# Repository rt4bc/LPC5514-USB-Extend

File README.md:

# LPC5514-USB-Extend
## Function
Create a board which integrated with CMSIS DAP interface for cortex MCU debugging, and extend with common digital interface, like I2C, SPI, UART, CAN, ADC, and GPIO(Including normal input and output function, also can working at bitbang mode, like FT232H chip).

## Hardware Architecture
### USB0/1 Interface
1. USB0, Full speed interface, reserved.
2. USB1, High speed interface, Custom HID device, for CMSIS-Dap interface and other extened interfaces, SPI, UART, I2C and CAN FD.
### 3D Layout

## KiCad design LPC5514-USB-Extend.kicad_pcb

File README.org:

* LPC5514-USB-Extend
** Function
Create a board which integrated with CMSIS DAP interface for cortex MCU debugging, and extend with common digital interface, like I2C, SPI, UART, CAN, ADC, and GPIO(Including normal input and output function, also can working at bitbang mode, like FT232H chip).

** Hardware Architecture
*** USB0/1 Interface
1. USB0, Full speed interface, reserved.
2. USB1, High speed interface, Custom HID device, for CMSIS-Dap interface and other extened interfaces, SPI, UART, I2C and CAN FD.
*** 3D Layout
[[file:LPC5514-USB-Extend.png][PCB 3D Layout]]

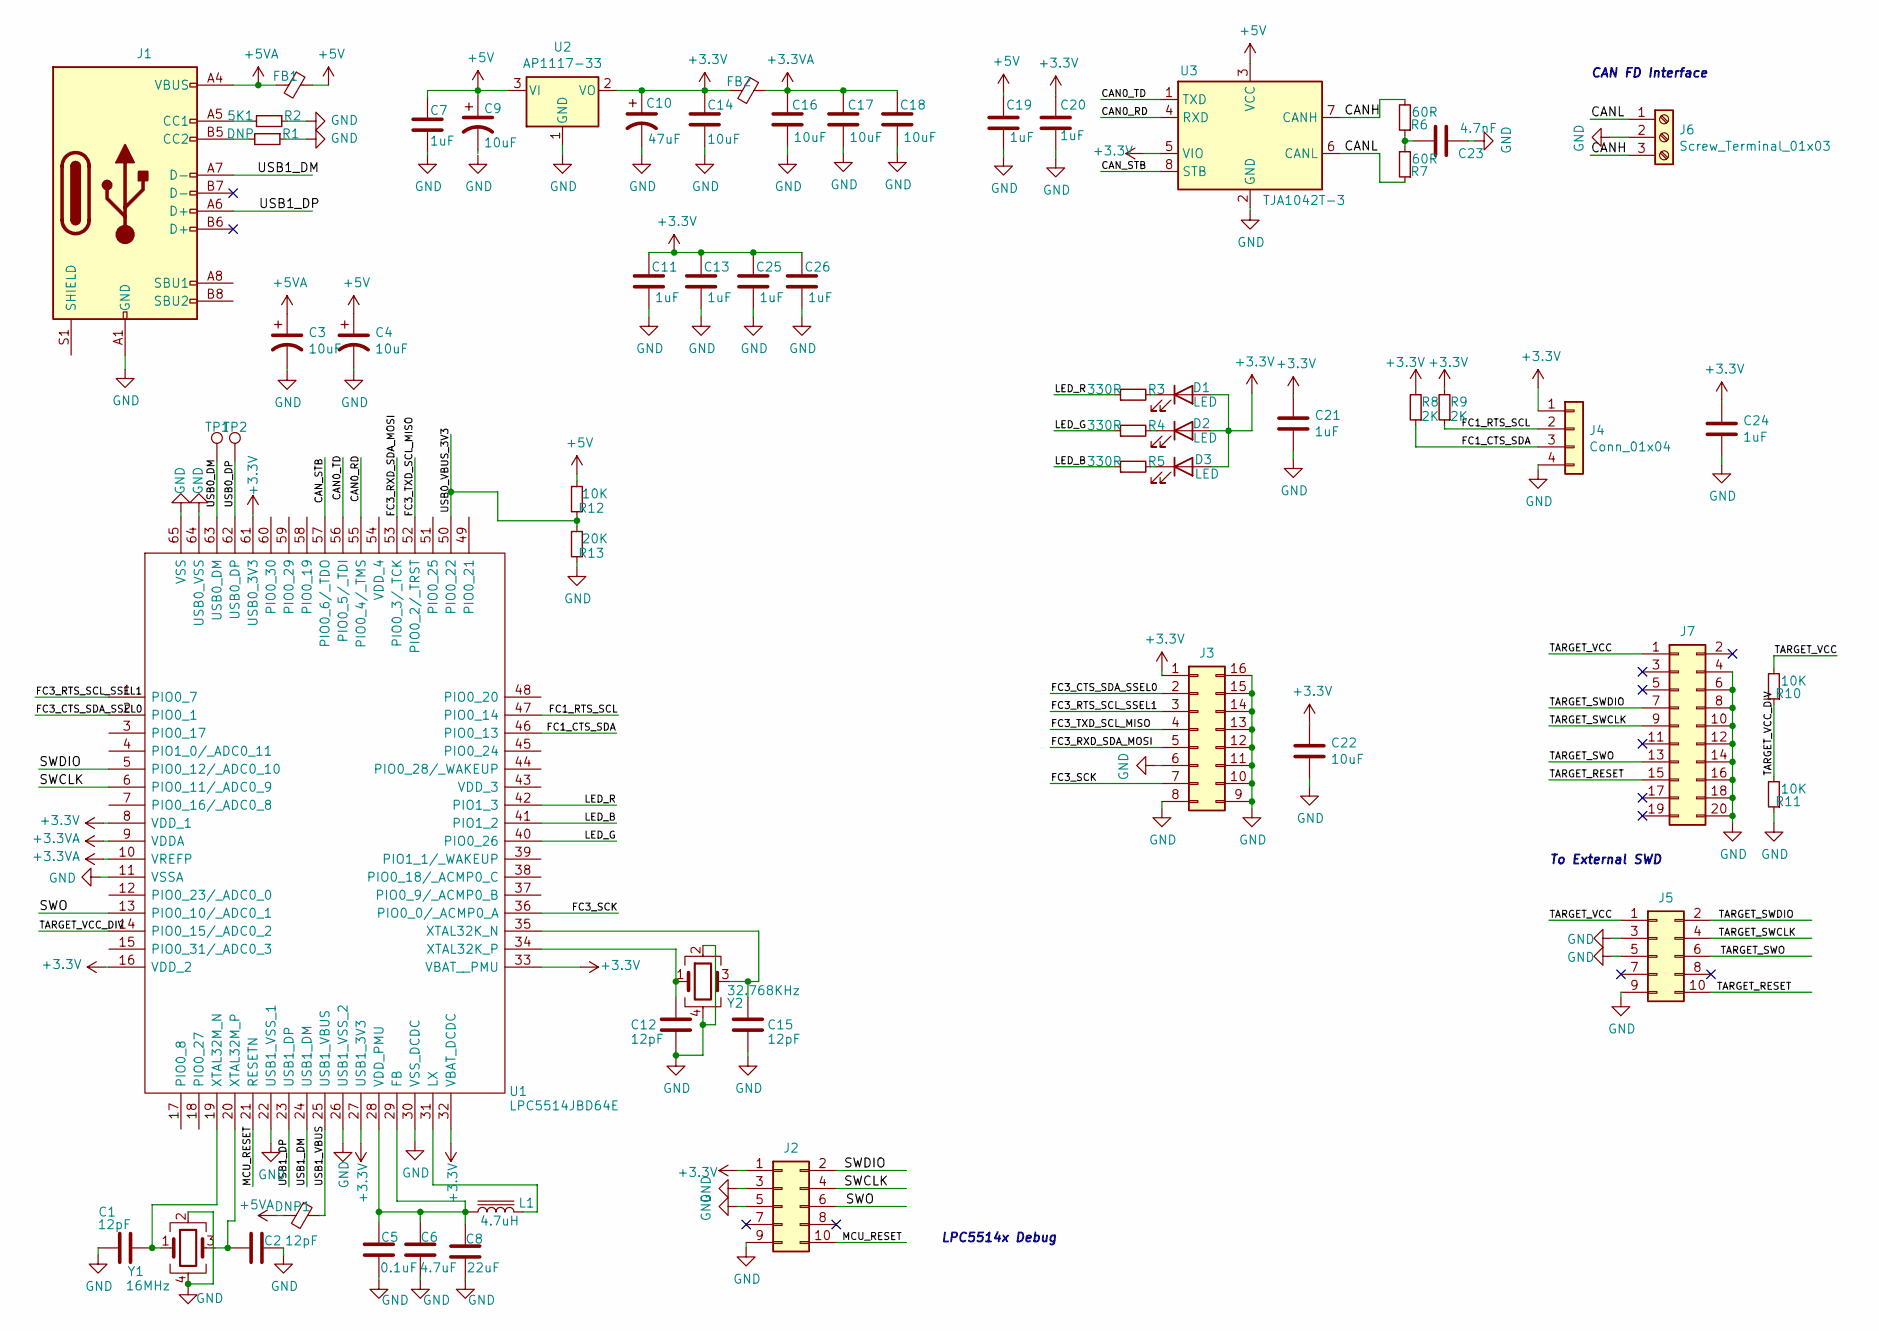
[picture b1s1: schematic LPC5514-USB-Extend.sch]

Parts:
C1, C2, C12, C15: 12pF; C_0603_1608Metric_Pad1.08x0.95mm_HandSolder
C3, C4, C9, C14, C16, C17, C18: 10uF; C_0805_2012Metric_Pad1.18x1.45mm_HandSolder
C5: 0.1uF; C_0603_1608Metric_Pad1.08x0.95mm_HandSolder
C6: 4.7uF; C_0805_2012Metric_Pad1.18x1.45mm_HandSolder
C7, C11, C13, C19, C20, C24, C25, C26: 1uF; C_0603_1608Metric_Pad1.08x0.95mm_HandSolder
C8: 22uF; C_0805_2012Metric_Pad1.18x1.45mm_HandSolder
C10: 47uF; C_0805_2012Metric_Pad1.18x1.45mm_HandSolder
C21: 1uF; C_0805_2012Metric_Pad1.18x1.45mm_HandSolder
C22: 10uF; C_0603_1608Metric_Pad1.08x0.95mm_HandSolder
C23: 4.7nF; C_0603_1608Metric_Pad1.08x0.95mm_HandSolder
D1, D2, D3: LED; LED_0603_1608Metric
DNP1: Ferrite_Bead_Small; L_0603_1608Metric
FB1, FB2: Ferrite_Bead_Small; L_0603_1608Metric
J1: USB_C_Receptacle_USB2.0; USB_C_Receptacle_HRO_TYPE-C-31-M-12
J2, J5: Conn_02x05_Odd_Even; PinHeader_2x05_P1.27mm_Vertical
J3: Conn_02x08_Counter_Clockwise; PinHeader_2x08_P2.54mm_Vertical
J4: Conn_01x04; PinHeader_1x04_P2.54mm_Vertical
J6: Screw_Terminal_01x03; PhoenixContact_MSTBA_2,5_3-G-5,08_1x03_P5.08mm_Horizontal
J7: Conn_02x10_Odd_Even; PinHeader_2x10_P2.54mm_Vertical
L1: 4.7uH; L_Wuerth_MAPI-2512
R1: DNP; R_0603_1608Metric
R2: 5K1; R_0603_1608Metric
R3, R4, R5: 330R; R_0603_1608Metric
R6, R7: 60R; R_0603_1608Metric
R8, R9: 2K; R_0603_1608Metric
R10, R11, R12: 10K; R_0603_1608Metric
R13: 20K; R_0603_1608Metric
TP1, TP2: TestPoint; TestPoint_Pad_1.0x1.0mm
U1: LPC5514JBD64E; QFP50P1200X1200X120-65N; Manufacturer_Part_Number LPC5514JBD64E; Mouser Part Number 771-LPC5514JBD64E
U2: AP1117-33; SOT-223-3_TabPin2
U3: TJA1042T-3; SOIC-8_3.9x4.9mm_P1.27mm
Y1: 16MHz; Oscillator_SMD_Abracon_ASE-4Pin_3.2x2.5mm
Y2: 32.768KHz; Oscillator_SMD_Abracon_ASE-4Pin_3.2x2.5mm

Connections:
+3.3VA: C16.1, C17.1, C18.1, FB2.1, U1.9 (VDDA), U1.10 (VREFP)
+3V3: C10.1, C11.1, C13.1, C14.1, C20.1, C21.1, C22.1, C24.1, C25.1, C26.1, D1.2 (A), D2.2 (A), D3.2 (A), FB2.2, J2.1, J3.1, J4.1, R8.2, R9.2, U1.8 (VDD_1), U1.16 (VDD_2), U1.27 (USB1_3V3), U1.32 (VBAT_DCDC), U1.33 (VBAT__PMU), U1.61 (USB0_3V3), U2.2 (VO), U3.5 (VIO)
+5V: C4.1, C7.1, C9.1, C19.1, FB1.1, R12.1, U2.3 (VI), U3.3 (VCC)
+5VA: C3.1, DNP1.2, FB1.2, J1.A4 (VBUS), J1.A9 (VBUS), J1.B4 (VBUS), J1.B9 (VBUS)
/CAN0_RD: U1.55 (PIO0_4/_TMS), U3.4 (RXD)
/CAN0_TD: U1.56 (PIO0_5/_TDI), U3.1 (TXD)
/CANH: J6.3, R6.2, U3.7 (CANH)
/CANL: J6.1, R7.1, U3.6 (CANL)
/CAN_STB: U1.57 (PIO0_6/_TDO), U3.8 (STB)
/FC1_CTS_SDA: J4.3, R8.1, U1.46 (PIO0_13)
/FC1_RTS_SCL: J4.2, R9.1, U1.47 (PIO0_14)
/FC3_CTS_SDA_SSEL0: J3.2, U1.2 (PIO0_1)
/FC3_RTS_SCL_SSEL1: J3.3, U1.1 (PIO0_7)
/FC3_RXD_SDA_MOSI: J3.5, U1.53 (PIO0_3/_TCK)
/FC3_SCK: J3.7, U1.36 (PIO0_0/_ACMP0_A)
/FC3_TXD_SCL_MISO: J3.4, U1.52 (PIO0_2/_TRST)
/LED_B: R5.1, U1.41 (PIO1_2)
/LED_G: R4.1, U1.40 (PIO0_26)
/LED_R: R3.1, U1.42 (PIO1_3)
/MCU_RESET: J2.10, U1.21 (RESETN)
/SWCLK: J2.4, U1.6 (PIO0_11/_ADC0_9)
/SWDIO: J2.2, U1.5 (PIO0_12/_ADC0_10)
/SWO: J2.6, U1.13 (PIO0_10/_ADC0_1)
/TARGET_RESET: J5.10, J7.15
/TARGET_SWCLK: J5.4, J7.9
/TARGET_SWDIO: J5.2, J7.7
/TARGET_SWO: J5.6, J7.13
/TARGET_VCC: J5.1, J7.1, R10.2
/TARGET_VCC_DIV: R10.1, R11.2, U1.14 (PIO0_15/_ADC0_2)
/USB0_DM: TP1.1, U1.63 (USB0_DM)
/USB0_DP: TP2.1, U1.62 (USB0_DP)
/USB0_VBUS_3V3: R12.2, R13.1, U1.50 (PIO0_22)
/USB1_DM: J1.A7 (D-), U1.24 (USB1_DM)
/USB1_DP: J1.A6 (D+), U1.23 (USB1_DP)
/USB1_VBUS: DNP1.1, U1.25 (USB1_VBUS)
GND: C1.2, C2.1, C3.2, C4.2, C5.1, C6.1, C7.2, C8.1, C10.2, C11.2, C12.1, C13.2, C14.2, C15.1, C16.2, C17.2, C18.2, C19.2, C20.2, C21.2, C22.2, C23.1, C24.2, C25.2, C26.2, J1.A1 (GND), J1.A12 (GND), J1.B1 (GND), J1.B12 (GND), J2.3, J2.5, J2.9, J3.6, J3.8, J3.9, J3.10, J3.11, J3.12, J3.13, J3.14, J3.15, J3.16, J4.4, J5.3, J5.5, J5.9, J6.2, J7.4, J7.6, J7.8, J7.10, J7.12, J7.14, J7.16, J7.18, J7.20, R1.1, R2.1, R11.1, R13.2, U1.11 (VSSA), U1.22 (USB1_VSS_1), U1.26 (USB1_VSS_2), U1.30 (VSS_DCDC), U1.64 (USB0_VSS), U1.65 (VSS), U2.1 (GND), U3.2 (GND), Y1.2, Y1.4, Y2.2, Y2.4
unnamed: C1.1, U1.19 (XTAL32M_N), Y1.1
unnamed: C2.2, U1.20 (XTAL32M_P), Y1.3
unnamed: C5.2, C6.2, C8.2, L1.1, U1.28 (VDD_PMU), U1.29 (FB)
unnamed: C12.2, U1.34 (XTAL32K_P), Y2.1
unnamed: C15.2, U1.35 (XTAL32K_N), Y2.3
unnamed: C23.2, R6.1, R7.2
unnamed: D1.1 (K), R3.2
unnamed: D2.1 (K), R4.2
unnamed: D3.1 (K), R5.2
unnamed: J1.A5 (CC1), R2.2
unnamed: J1.B5 (CC2), R1.2
unnamed: L1.2, U1.31 (LX)

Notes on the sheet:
To External SWD
LPC5514x Debug
CAN FD Interface

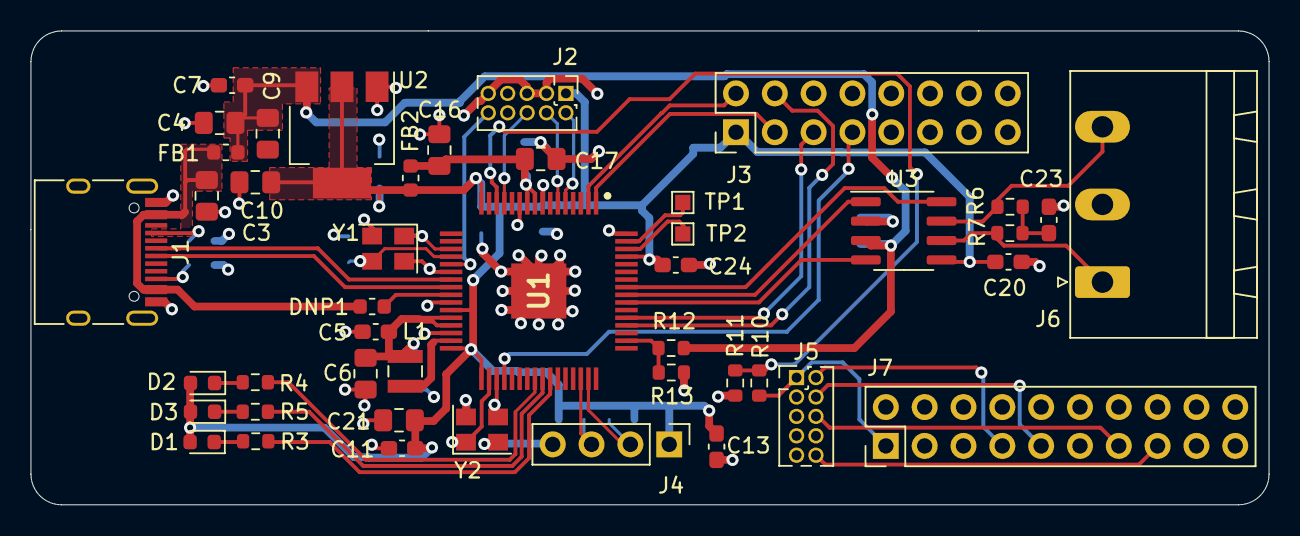
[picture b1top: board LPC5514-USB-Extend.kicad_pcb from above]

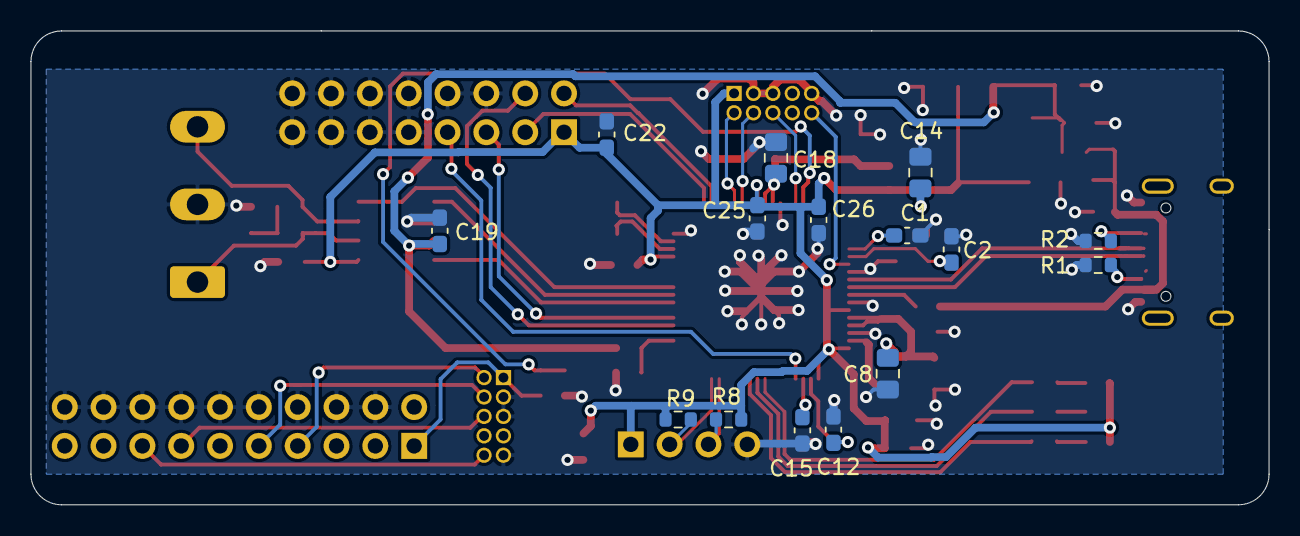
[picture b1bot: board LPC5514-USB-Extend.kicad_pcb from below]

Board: 2 copper layers, 81.0 x 31.0 mm, 60 parts (15 on the bottom side), 48 nets.

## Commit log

2021-05-27 remove unused fiels
2021-05-27 rm files
2021-05-27 rename README
2021-05-27 README.org
2021-05-28 create system document.
2021-06-06 update design, usb0/1 connection & power
2021-06-06 update description.
2021-06-15 update sch and add footprint
2021-06-16 update pcb
2021-06-20 update design
2021-06-20 Add PCB 3D Layout in readme file
2021-06-20 update file path
2021-06-20 rename readme file
2021-06-20 update link
2021-06-20 fix link
2021-06-21 update pcb & add data manual
